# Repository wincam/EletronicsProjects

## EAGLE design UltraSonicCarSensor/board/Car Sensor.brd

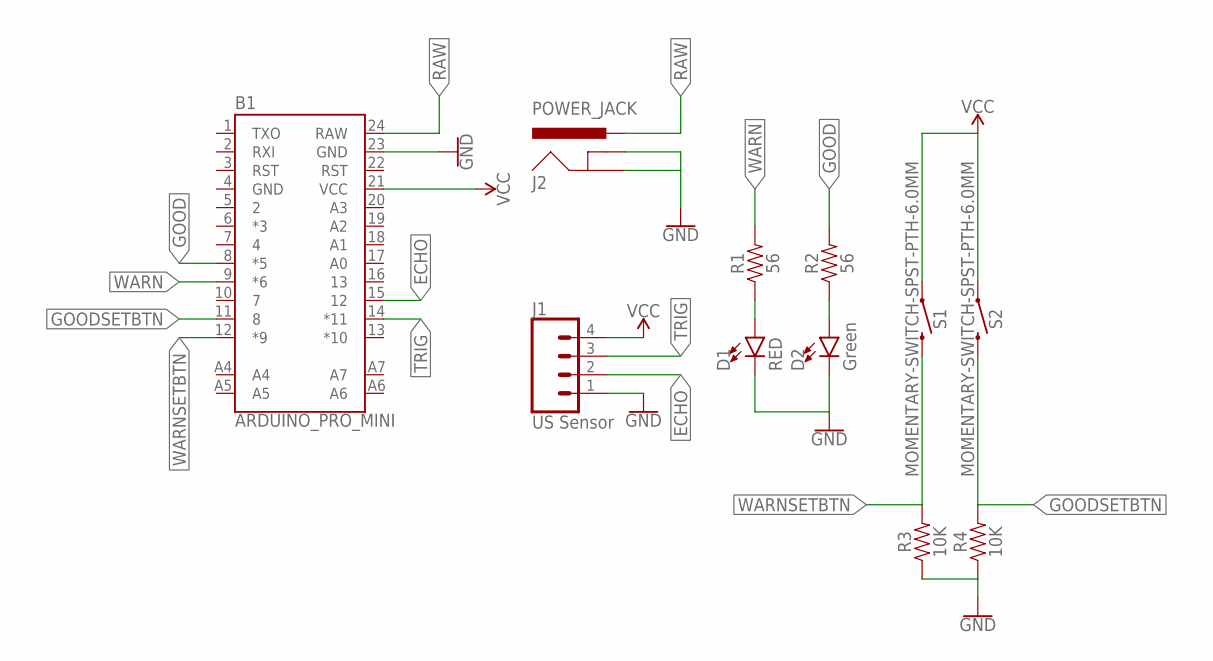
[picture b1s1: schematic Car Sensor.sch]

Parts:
B1: ARDUINO_PRO_MINI
D1: RED; LED_5MM
D2: Green; LED_5MM
J1: US Sensor; 1X04_SMD_RA_FEMALE
J2: POWER_JACK; POWER_JACK_PTH
R1, R2: 56; 0805
R3, R4: 10K; 0805
S1, S2: MOMENTARY-SWITCH-SPST-PTH-6.0MM; TACTILE_SWITCH_PTH_6.0MM

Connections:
ECHO: B1.15 (12), J1.2
GND: B1.4 (GND), B1.23 (GND), D1.K (C), D2.K (C), J1.1, J2.GND, J2.GNDBREAK, R3.1, R4.1
GOOD: B1.8 (*5), R2.2
GOODSETBTN: B1.11 (8), R4.2, S2.3 (2)
unnamed: D1.A, R1.1
unnamed: D2.A, R2.1
RAW: B1.24 (RAW), J2.PWR
TRIG: B1.14 (*11), J1.3
VCC: B1.21 (VCC), J1.4, S1.1, S2.1
WARN: B1.9 (*6), R1.2
WARNSETBTN: B1.12 (*9), R3.2, S1.3 (2)

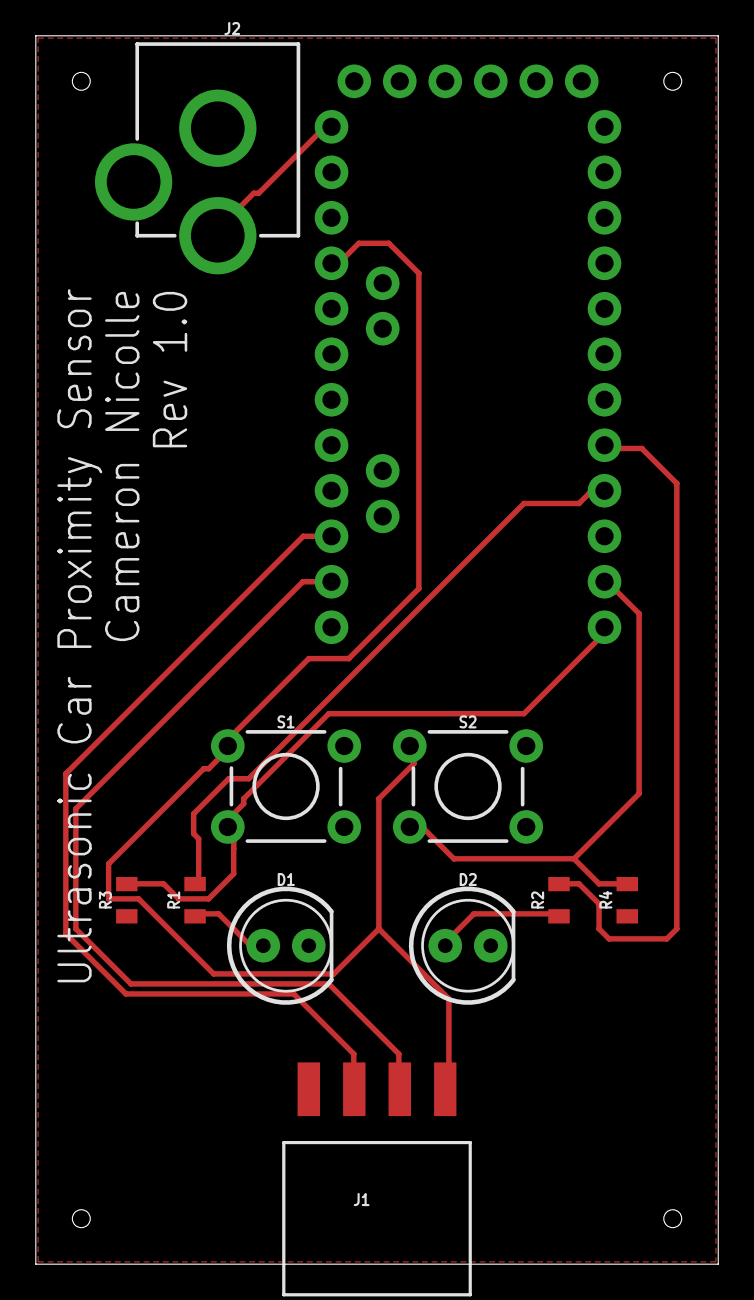
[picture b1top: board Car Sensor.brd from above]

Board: 2 copper layers, 38.1 x 68.6 mm, 11 parts (1 on the bottom side), 11 nets.

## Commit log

2017-09-07 sent ultrasonic sensor to fab

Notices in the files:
parts and their libraries:
SparkFun-Boards: Licensing: Creative Commons ShareAlike 4.0 International - https://creativecommons.org/licenses/by-sa/4.0
